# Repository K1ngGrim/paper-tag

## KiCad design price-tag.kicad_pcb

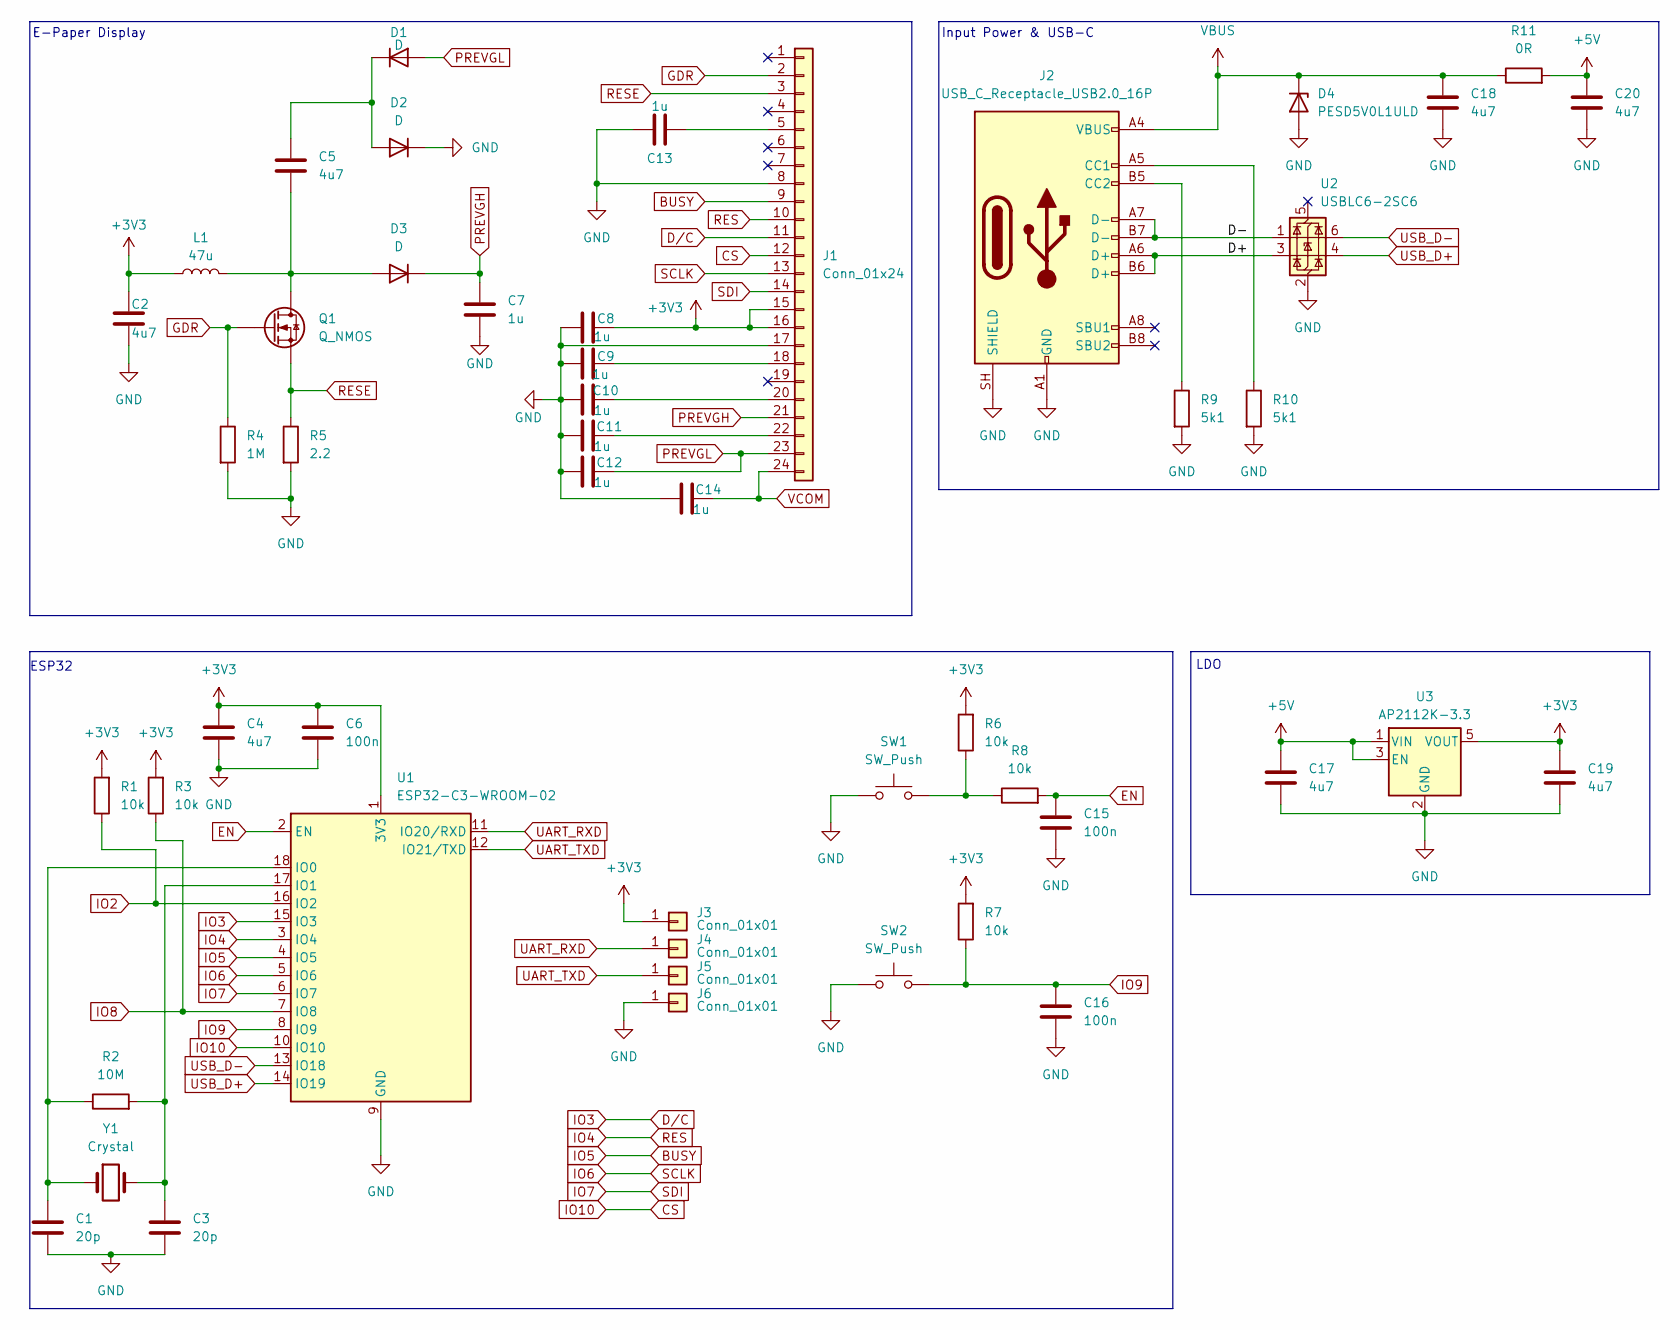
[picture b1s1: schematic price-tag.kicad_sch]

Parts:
C1, C3: 20p; C_0603_1608Metric
C2, C4, C5, C17, C18, C19, C20: 4u7; C_0805_2012Metric
C6, C15, C16: 100n; C_0603_1608Metric
C7, C8, C9, C10, C11, C12, C13, C14: 1u; C_0603_1608Metric
D1, D2, D3: D; D_SOD-123
D4: PESD5V0L1ULD; D_SOD-882
J1: Conn_01x24; Hirose_FH12-24S-0.5SH_1x24-1MP_P0.50mm_Horizontal
J2: USB_C_Receptacle_USB2.0_16P; USB_C_Receptacle_GCT_USB4105-xx-A_16P_TopMnt_Horizontal
J3, J4, J5, J6: Conn_01x01; TestPoint_Pad_D1.0mm
L1: 47u; L_Wuerth_WE-TPC-3816
Q1: Q_NMOS; SOT-323_SC-70
R1, R3, R6, R7, R8: 10k; R_0603_1608Metric
R2: 10M; R_0603_1608Metric
R4: 1M; R_0603_1608Metric
R5: 2.2; R_0603_1608Metric
R9, R10: 5k1; R_0603_1608Metric
R11: 0R; R_0603_1608Metric
SW1, SW2: SW_Push; SW_SPST_B3U-1000P
U1: ESP32-C3-WROOM-02
U2: USBLC6-2SC6; SOT-23-6
U3: AP2112K-3.3; SOT-23-5
Y1: Crystal; CM7V32768TBQA020

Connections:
+3V3: C2.2, C4.1, C6.1, C8.2, C19.1, J1.15, J1.16, J3.1 (Pin_1_1), L1.1, R1.2, R3.2, R6.2, R7.2, U1.1 (3V3), U3.5 (VOUT)
+5V: C17.1, C20.1, R11.2, U3.1 (VIN), U3.3 (EN)
/D+: J2.A6 (D+), J2.B6 (D+), U2.3 (I/O2)
/D-: J2.A7 (D-), J2.B7 (D-), U2.1 (I/O1)
BUSY: J1.9, U1.4 (IO5)
CS: J1.12, U1.10 (IO10)
D/C: J1.11, U1.15 (IO3)
EN: C15.1, R8.2, U1.2 (EN)
GDR: J1.2, Q1.1 (G), R4.1
GND: C1.2, C2.1, C3.2, C4.2, C6.2, C7.1, C8.1, C9.1, C10.1, C11.1, C12.1, C13.1, C14.1, C15.2, C16.2, C17.2, C18.2, C19.2, C20.2, D2.1 (K), D4.2 (A), J1.8, J1.17, J2.A1 (GND), J2.A12 (GND), J2.B1 (GND), J2.B12 (GND), J2.SH (SHIELD), J6.1 (Pin_1_1), R4.2, R5.2, R9.2, R10.2, SW1.1, SW2.1, U1.9 (GND), U1.19 (GND), U2.2 (GND), U3.2 (GND)
IO2: R1.1, U1.16 (IO2)
IO4: J1.10, U1.3 (IO4)
IO6: J1.13, U1.5 (IO6)
IO7: J1.14, U1.6 (IO7)
IO8: R3.1, U1.7 (IO8)
IO9: C16.1, R7.1, SW2.2, U1.8 (IO9)
unnamed: C5.2, D1.1 (K), D2.2 (A)
unnamed: C5.1, D3.2 (A), L1.2, Q1.3 (D)
unnamed: C13.2, J1.5
unnamed: C9.2, J1.18
unnamed: C10.2, J1.20
unnamed: C11.2, J1.22
unnamed: J2.A5 (CC1), R10.1
unnamed: J2.B5 (CC2), R9.1
unnamed: R6.1, R8.1, SW1.2
unnamed: C1.1, R2.1, U1.18 (IO0), Y1.1
unnamed: C3.1, R2.2, U1.17 (IO1), Y1.2
PREVGH: C7.2, D3.1 (K), J1.21
PREVGL: C12.2, D1.2 (A), J1.23
RESE: J1.3, Q1.2 (S), R5.1
UART_RXD: J4.1 (Pin_1_1), U1.11 (IO20/RXD)
UART_TXD: J5.1 (Pin_1_1), U1.12 (IO21/TXD)
USB_D+: U1.14 (IO19), U2.4 (I/O2)
USB_D-: U1.13 (IO18), U2.6 (I/O1)
VBUS: C18.1, D4.1 (K), J2.A4 (VBUS), J2.A9 (VBUS), J2.B4 (VBUS), J2.B9 (VBUS), R11.1
VCOM: C14.2, J1.24

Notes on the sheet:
LDO
Input Power & USB-C
E-Paper Display
ESP32

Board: 2 copper layers, 49 parts (0 on the bottom side), 36 nets, no tracks yet.
